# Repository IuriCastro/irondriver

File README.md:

# IronDriver

Soldering Iron controller

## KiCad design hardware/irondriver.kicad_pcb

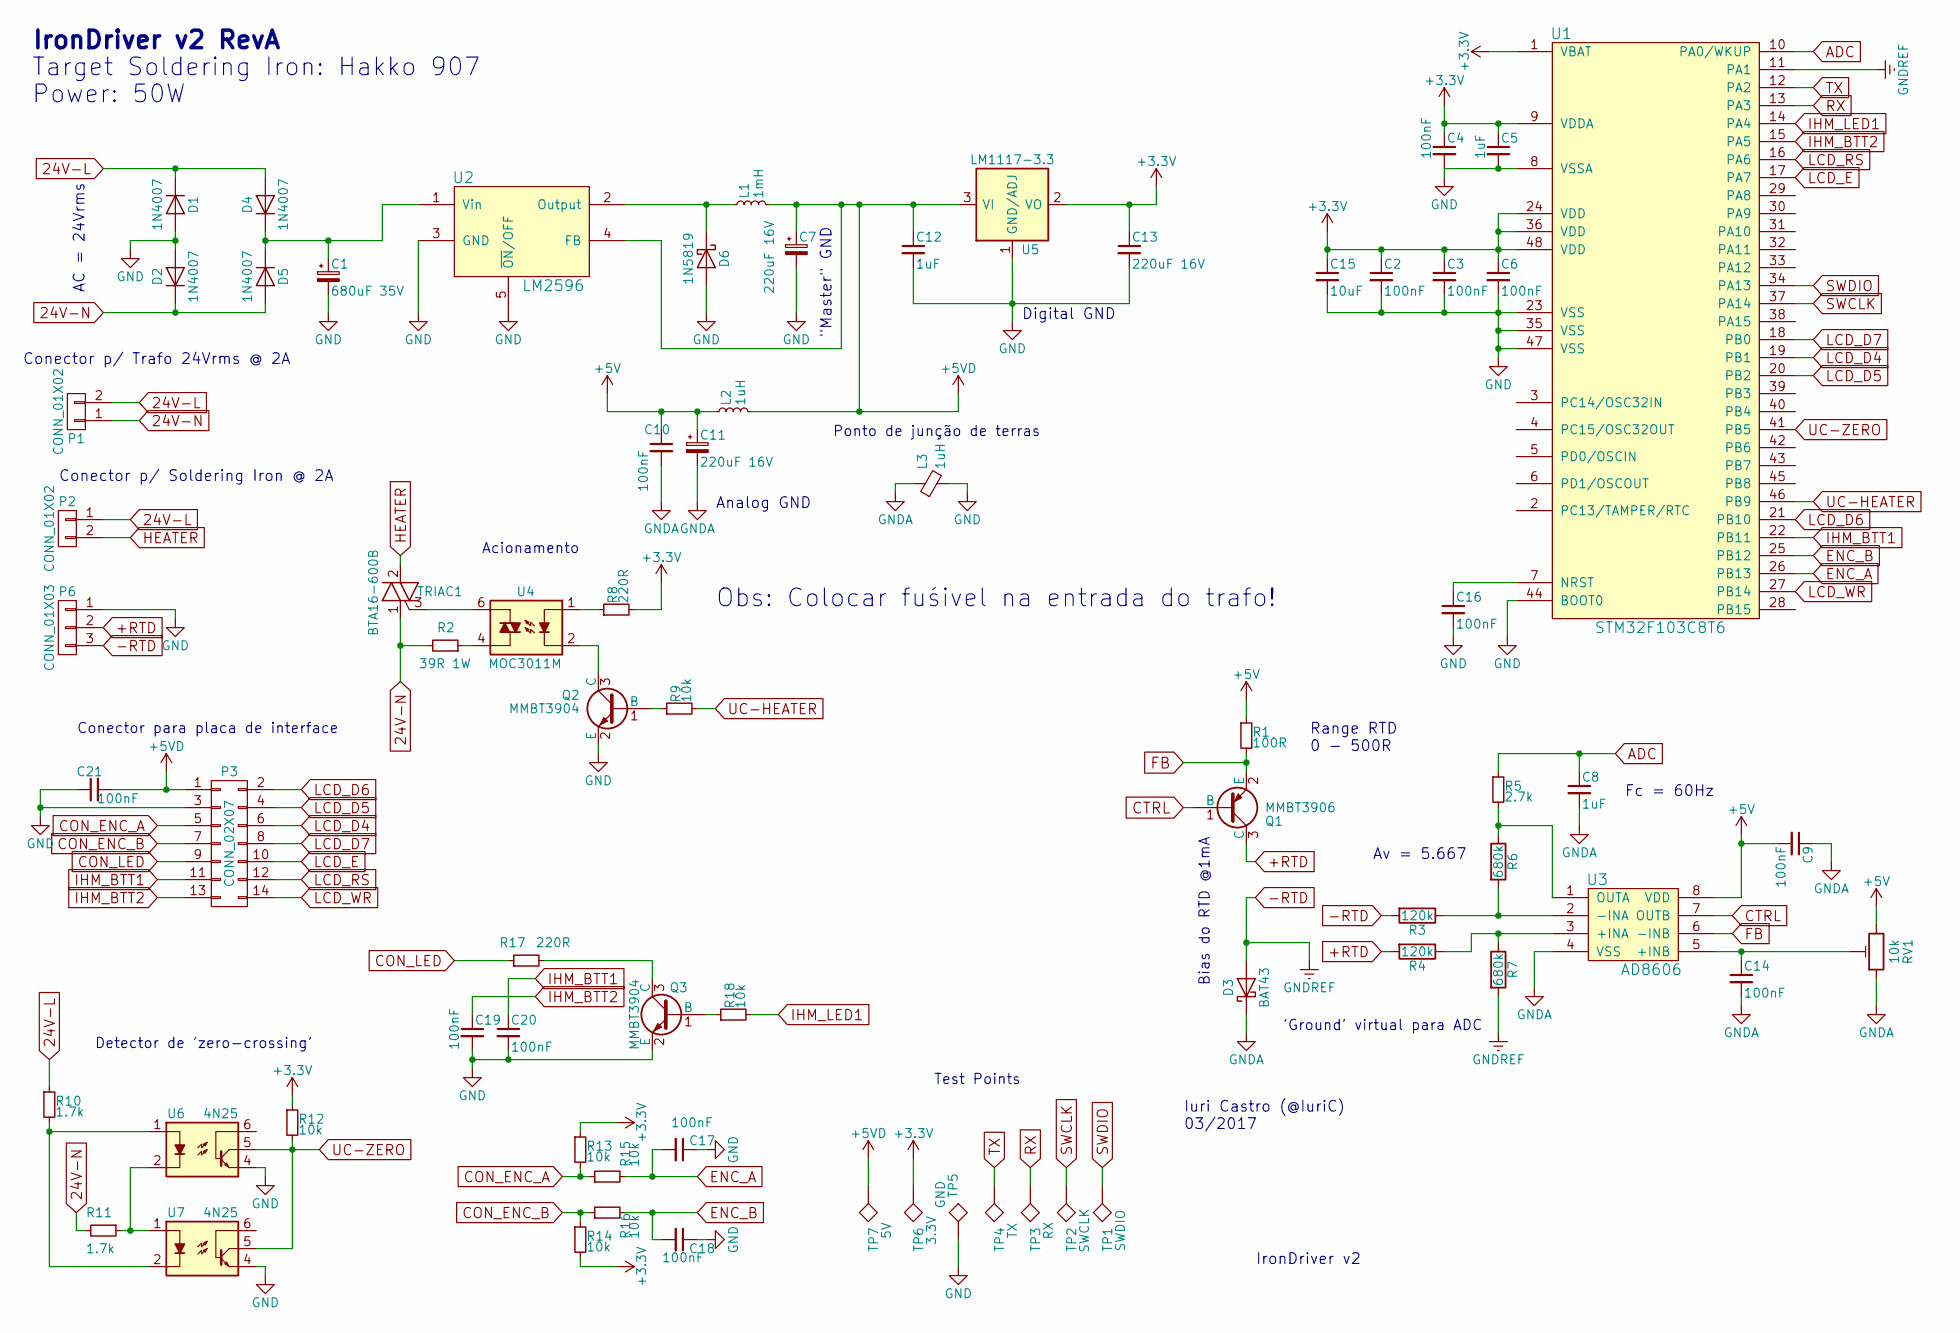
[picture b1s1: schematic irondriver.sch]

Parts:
C1: 680uF 35V; CP_Radial_D10.0mm_P5.00mm
C2, C3, C4, C6, C9, C10, C14, C16, C17, C18, C19, C20, C21: 100nF; C_0805
C5, C8: 1uF; C_0805
C7, C11, C13: 220uF 16V; CP_Radial_Tantal_D6.0mm_P2.50mm
C12: 1uF; C_0805_HandSoldering
C15: 10uF; C_0805
D1, D2, D4, D5: 1N4007; D_SMA_Standard
D3: BAT43; D_MELF_Standard
D6: 1N5819; D_DO-41_SOD81_P7.62mm_Horizontal
L1: 1mH; SELF-WE-PD3S
L2: 1uH; R_0805
L3: 1uH; R_0805_HandSoldering
P1, P2: CONN_01X02; bornier2
P3: CONN_02X07; IDC_Header_Straight_14pins
P6: CONN_01X03; Socket_Strip_Straight_1x03_Pitch2.54mm
Q1: MMBT3906; SOT-23
Q2, Q3: MMBT3904; SOT-23
R1: 100R; R_0805
R2: 39R 1W; R_2512
R3, R4: 120k; R_0805
R5: 2.7k; R_0805
R6, R7: 680k; R_0805
R8, R17: 220R; R_0805
R9, R12, R13, R14, R15, R16, R18: 10k; R_0805
R10, R11: 1.7k; R_0805
RV1: 10k; Potentiometer_Trimmer_Bourns_3266Y
TP1: SWDIO; Measurement_Point_Round-SMD-Pad_Big
TP2: SWCLK; Measurement_Point_Round-SMD-Pad_Big
TP3: RX; Measurement_Point_Round-SMD-Pad_Big
TP4: TX; Measurement_Point_Round-SMD-Pad_Big
TP5: GND; Measurement_Point_Round-SMD-Pad_Big
TP6: 3.3V; Measurement_Point_Round-SMD-Pad_Big
TP7: 5V; Measurement_Point_Round-SMD-Pad_Big
TRIAC1: BTA16-600B; TO-220_Vertical
U1: STM32F103C8T6; LQFP-48_7x7mm_Pitch0.5mm
U2: LM2596; TO-263-5Lead
U3: AD8606; MSOP-8_3x3mm_Pitch0.65mm
U4: MOC3011M; DIP-6_W7.62mm
U5: LM1117-3.3; SOT-223
U6, U7: 4N25; DIP-6_W7.62mm

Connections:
24V-L: D1.1 (K), D4.2 (A), P1.2, P2.1, R10.1
24V-N: D2.1 (K), D5.2 (A), P1.1, R2.2, R11.2, TRIAC1.1 (A2)
+3V3: C2.1, C3.1, C4.1, C5.1, C6.1, C13.1, C15.1, R8.2, R12.1, R13.1, R14.2, TP6.1, U1.1 (VBAT), U1.9 (VDDA), U1.24 (VDD), U1.36 (VDD), U1.48 (VDD), U5.2 (VO), U5.4 (VO)
+5V: C9.2, C10.1, C11.1, L2.1, R1.1, RV1.3, U3.8 (VDD)
+5VD: C7.1, C12.1, C21.2, L1.2, L2.2, P3.1, TP7.1, U2.4 (FB), U5.3 (VI)
+RTD: P6.2, Q1.3 (C), R4.2
-RTD: D3.2 (A), P6.3, R3.2, R7.2, U1.11 (PA1)
ADC: C8.1, R5.1, U1.10 (PA0/WKUP)
CON_ENC_A: P3.5, R13.2, R15.1
CON_ENC_B: P3.7, R14.1, R16.1
CON_LED: P3.9, R17.1
CTRL: Q1.1 (B), U3.7 (OUTB)
ENC_A: C17.2, R15.2, U1.26 (PB13)
ENC_B: C18.2, R16.2, U1.25 (PB12)
FB: Q1.2 (E), R1.2, U3.6 (-INB)
GND: C1.2, C2.2, C3.2, C4.2, C5.2, C6.2, C7.2, C12.2, C13.2, C15.2, C16.2, C17.1, C18.1, C19.2, C20.2, C21.1, D1.2 (A), D2.2 (A), D6.2 (A), L3.2, P3.3, P6.1, Q2.2 (E), Q3.2 (E), TP5.1, U1.8 (VSSA), U1.23 (VSS), U1.35 (VSS), U1.44 (BOOT0), U1.47 (VSS), U2.3 (GND), U2.5 (~ON~/OFF), U5.1 (GND/ADJ), U6.4, U7.4
GNDA: C8.2, C9.1, C10.2, C11.2, C14.2, D3.1 (K), L3.1, RV1.1, U3.4 (VSS)
HEATER: P2.2, TRIAC1.2 (A1)
IHM_BTT1: C20.1, P3.11, U1.22 (PB11)
IHM_BTT2: C19.1, P3.13, U1.15 (PA5)
IHM_LED1: R18.2, U1.14 (PA4)
LCD_D4: P3.6, U1.19 (PB1)
LCD_D5: P3.4, U1.20 (PB2)
LCD_D6: P3.2, U1.21 (PB10)
LCD_D7: P3.8, U1.18 (PB0)
LCD_E: P3.10, U1.17 (PA7)
LCD_RS: P3.12, U1.16 (PA6)
LCD_WR: P3.14, U1.27 (PB14)
unnamed: C1.1, D4.1 (K), D5.1 (K), U2.1 (Vin)
unnamed: C14.1, RV1.2, U3.5 (+INB)
unnamed: C16.1, U1.7 (NRST)
unnamed: D6.1 (K), L1.1, U2.2 (Output)
unnamed: Q2.1 (B), R9.1
unnamed: Q2.3 (C), U4.2
unnamed: Q3.1 (B), R18.1
unnamed: Q3.3 (C), R17.2
unnamed: R2.1, U4.4
unnamed: R3.1, R6.2, U3.2 (-INA)
unnamed: R4.1, R7.1, U3.3 (+INA)
unnamed: R5.2, R6.1, U3.1 (OUTA)
unnamed: R8.1, U4.1
unnamed: R10.2, U6.1, U7.2
unnamed: R11.1, U6.2, U7.1
unnamed: TRIAC1.3 (G), U4.6
RX: TP3.1, U1.13 (PA3)
SWCLK: TP2.1, U1.37 (PA14)
SWDIO: TP1.1, U1.34 (PA13)
TX: TP4.1, U1.12 (PA2)
UC-HEATER: R9.2, U1.46 (PB9)
UC-ZERO: R12.2, U1.41 (PB5), U6.5, U7.5

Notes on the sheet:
Fc = 60Hz
AC = 24Vrms
"Master" GND
Digital GND
Analog GND
Conector p/ Trafo 24Vrms @ 2A
Conector p/ Soldering Iron @ 2A
Av = 5.667
Range RTD 0 - 500R
Iuri Castro (@IuriC) 03/2017
IronDriver v2
Acionamento
Detector de 'zero-crossing'
Ponto de junção de terras
'Ground' virtual para ADC
Test Points
Bias do RTD @1mA
IronDriver v2 RevA
Obs: Colocar fuśivel na entrada do trafo!
Target Soldering Iron: Hakko 907
Power: 50W
Conector para placa de interface

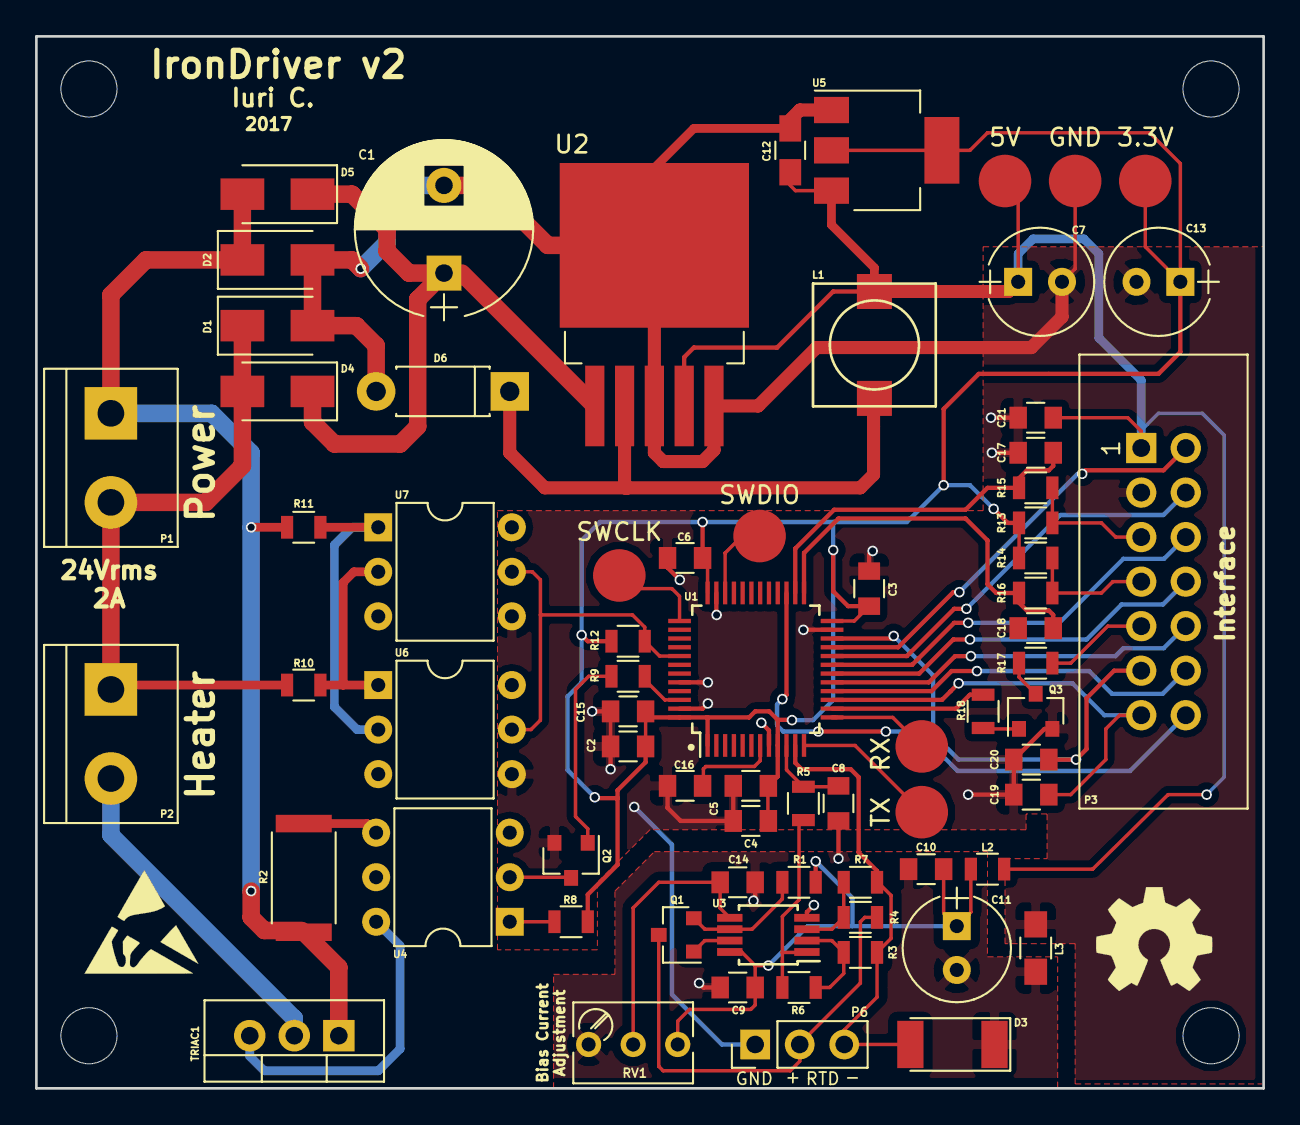
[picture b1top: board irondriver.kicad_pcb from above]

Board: 2 copper layers, 70.0 x 60.0 mm, 71 parts (0 on the bottom side), 50 nets.

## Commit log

2017-04-08 Inital commit
2017-04-11 Changed silk placement and size. Added logo and author information.
2017-05-28 Added some info to README.md
2017-10-05 Changed README info
